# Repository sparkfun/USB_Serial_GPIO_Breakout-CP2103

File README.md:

SparkFun USB to Serial GPIO Breakout - CP2103
========================================

[*SparkFun USB to Serial GPIO Breakout - CP2103(BOB-00199)*](https://www.sparkfun.com/products/199)

Basic breakout board for the new Silicon Laboratories' CP2103 USB to Serial IC.

Repository Contents
-------------------

* **/Hardware** - Eagle design files (.brd, .sch)
* **/Production** - Production panel files (.brd)

Documentation
--------------
* **[SparkFun Fritzing repo](https://github.com/sparkfun/Fritzing_Parts)** - Fritzing diagrams for SparkFun products.
* **[SparkFun 3D Model repo](https://github.com/sparkfun/3D_Models)** - 3D models of SparkFun products. 

License Information
-------------------
This product is _**open source**_! 

The **hardware** is released under [Creative Commons ShareAlike 4.0 International](https://creativecommons.org/licenses/by-sa/4.0/).

Please use, reuse, and modify these files as you see fit. Please maintain attribution to SparkFun Electronics and release anything derivative under the same license.

Distributed as-is; no warranty is given.

- Your friends at SparkFun.

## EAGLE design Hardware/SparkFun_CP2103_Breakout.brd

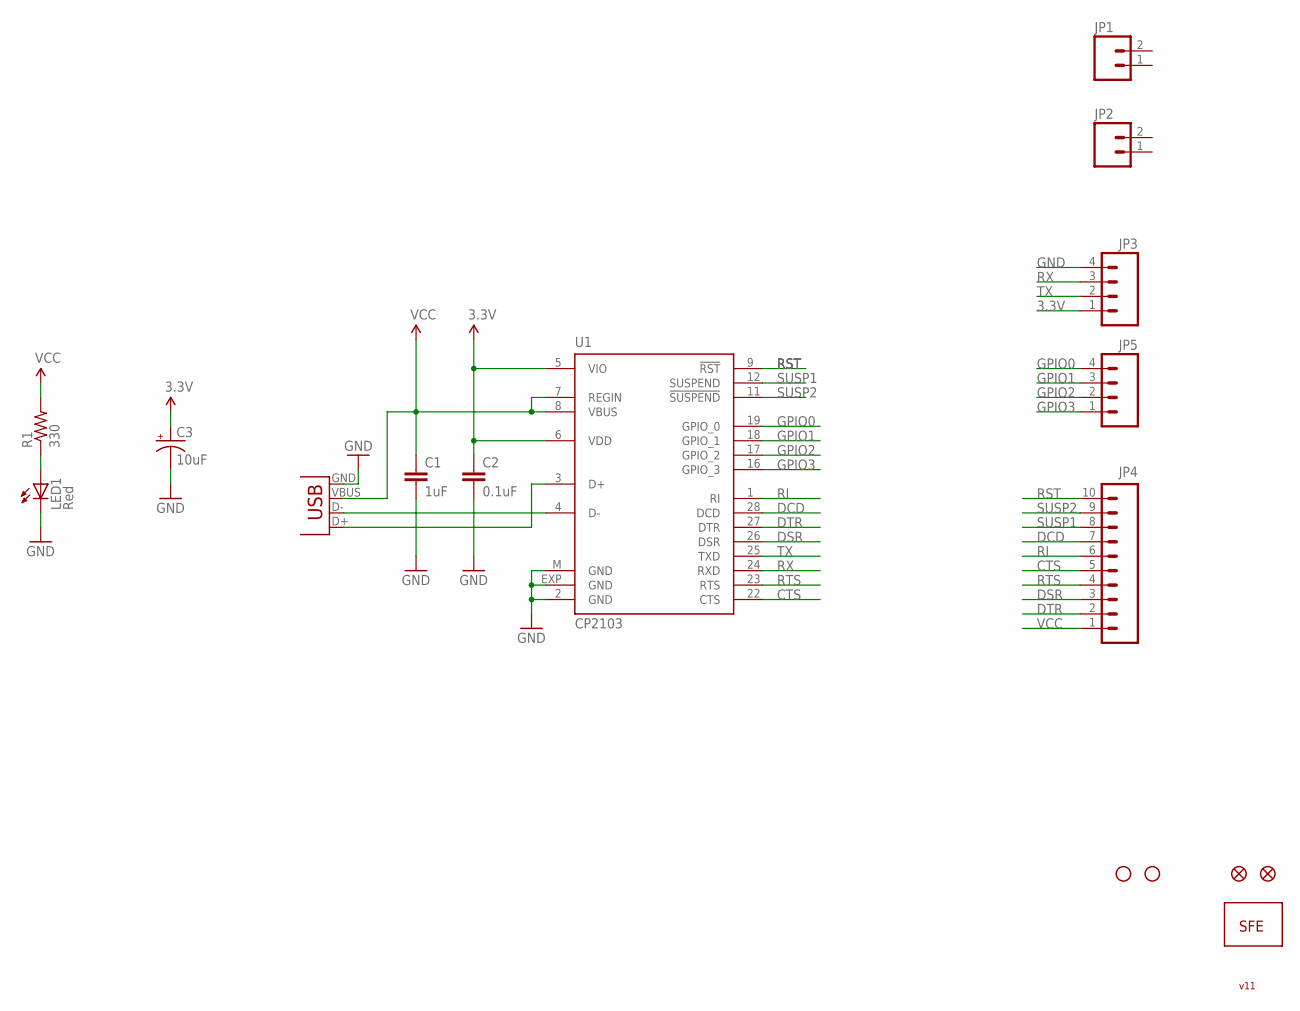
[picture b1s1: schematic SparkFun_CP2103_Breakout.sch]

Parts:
C1: 1uF; C0402
C2: 0.1uF; C0402
C3: 10uF; EIA3216
JP1, JP2: M02PTH; 1X02
JP3, JP5: M04PTH; 1X04
JP4: M100.1; 1X10
LED1: Red; LED-1206
R1: 330; C0402
U1: CP2103; MLP28
U$1: LOGO-SFENEW; SFE-NEW-WEBLOGO
U$2, U$3: FIDUCIAL1X2; FIDUCIAL-1X2
U$6, U$7: STAND-OFF
X1: USBPTH; USB-B-PTH

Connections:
3.3V: C2.1, C3.A (+), JP3.1, U1.5 (VIO), U1.6 (VDD)
CTS: JP4.5, U1.22 (CTS)
D+: U1.3 (D+), X1.D+
D-: U1.4 (D-), X1.D-
DCD: JP4.7, U1.28 (DCD)
DSR: JP4.3, U1.26 (DSR)
DTR: JP4.2, U1.27 (DTR)
GND: C1.2, C2.2, C3.C (-), JP3.4, LED1.C, U1.2 (GND), U1.EXP (GND), U1.M (GND), X1.GND
GPIO0: JP5.4, U1.19 (GPIO_0)
GPIO1: JP5.3, U1.18 (GPIO_1)
GPIO2: JP5.2, U1.17 (GPIO_2)
GPIO3: JP5.1, U1.16 (GPIO_3)
unnamed: LED1.A, R1.1
RI: JP4.6, U1.1 (RI)
RST: JP4.10, U1.9 (!RST)
RTS: JP4.4, U1.23 (RTS)
RX: JP3.3, U1.24 (RXD)
SUSP1: JP4.8, U1.12 (SUSPEND)
SUSP2: JP4.9, U1.11 (!SUSPEND)
TX: JP3.2, U1.25 (TXD)
VCC: C1.1, JP4.1, R1.2, U1.7 (REGIN), U1.8 (VBUS), X1.VBUS

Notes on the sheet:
v11

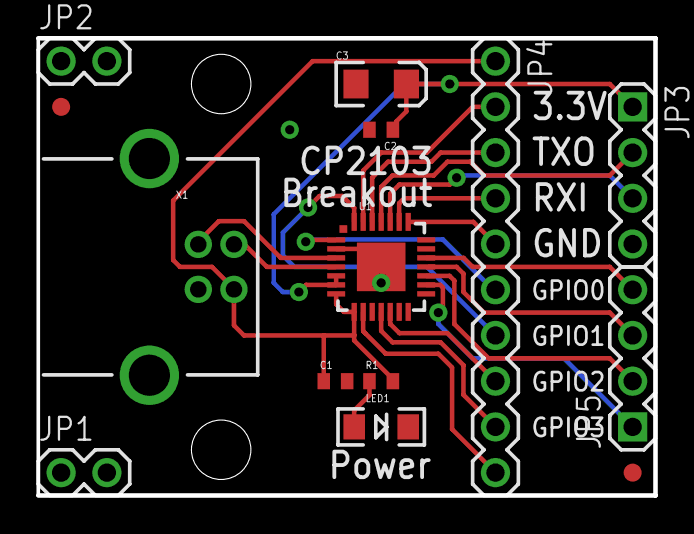
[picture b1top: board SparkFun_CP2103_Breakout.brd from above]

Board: 2 copper layers, 34.3 x 25.4 mm, 17 parts (1 on the bottom side), 21 nets.

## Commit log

2015-05-11 Adding hardware files
2015-05-11 Updating license file
2015-05-11 Updating hardware files
